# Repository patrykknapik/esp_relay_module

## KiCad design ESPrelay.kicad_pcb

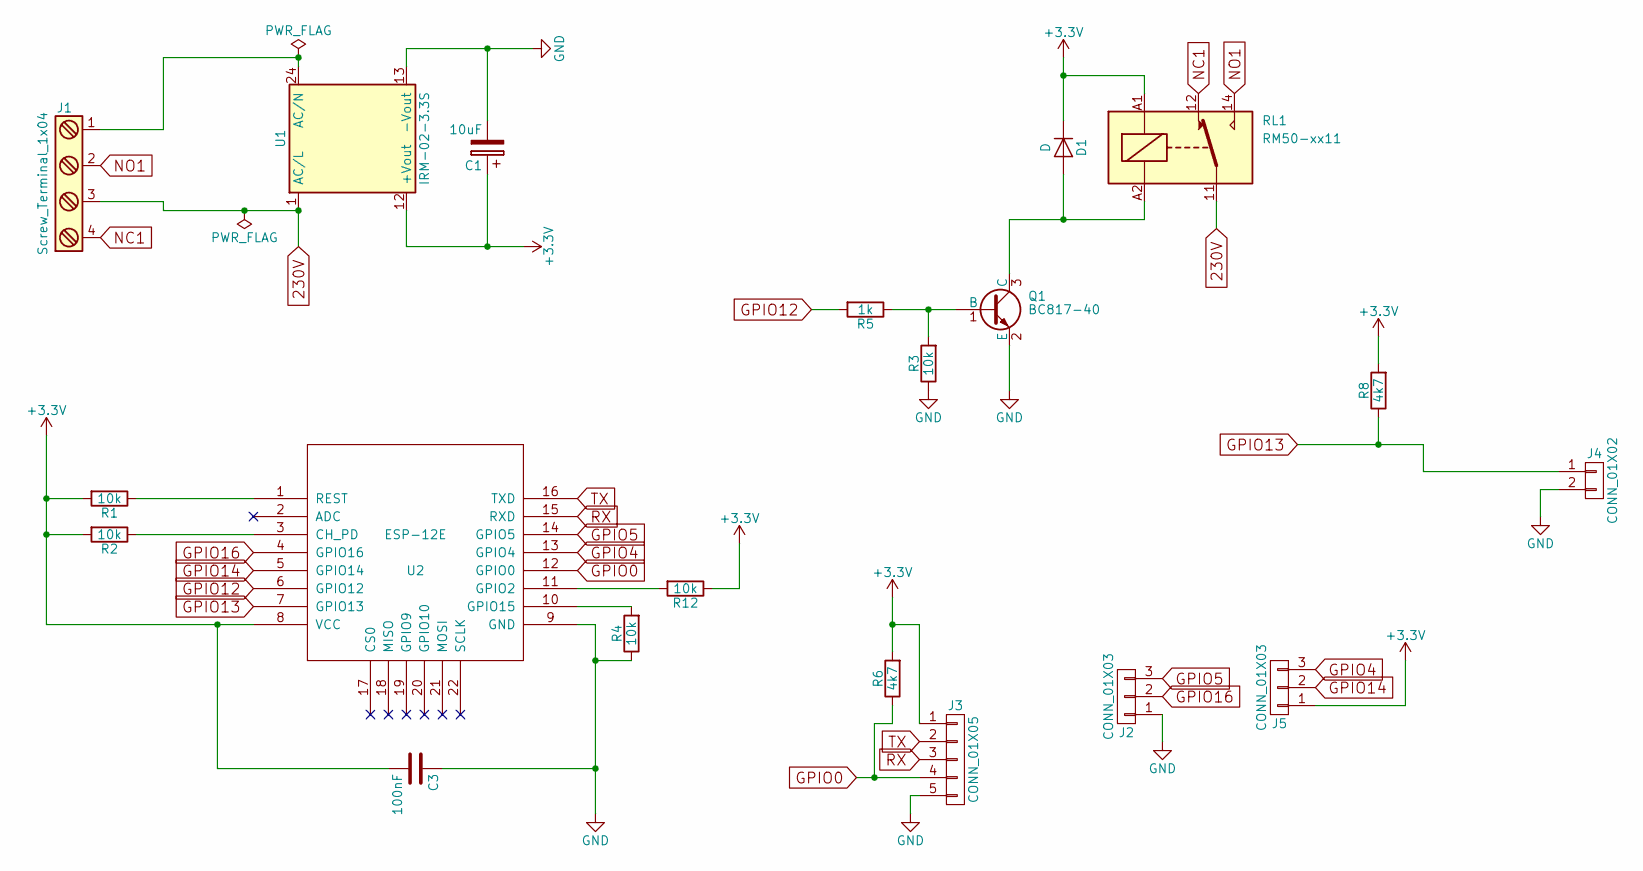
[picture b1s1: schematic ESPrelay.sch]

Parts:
C1: 10uF; CP_Tantalum_Case-B_EIA-3528-21_Hand
C3: 100nF; C_0805_HandSoldering
D1: D; D_MiniMELF_Handsoldering
J1: Screw_Terminal_1x04; bornier4
J2, J5: CONN_01X03; Pin_Header_Straight_1x03_Pitch2.54mm
J3: CONN_01X05; Pin_Header_Straight_1x05_Pitch2.54mm
J4: CONN_01X02; Pin_Header_Straight_1x02_Pitch2.54mm
Q1: BC817-40; SOT-23_Handsoldering
R1, R2, R3, R4, R12: 10k; R_0805_HandSoldering
R5: 1k; R_0805_HandSoldering
R6, R8: 4k7; R_0805_HandSoldering
RL1: RM50-xx11; Relpol_RM50-3011
U1: IRM-02-3.3S; ACDC-Converter_MeanWell-IRM-02-XS
U2: ESP-12E; ESP-12E_SMD

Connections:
230V: J1.3, RL1.11, U1.1 (AC/L)
+3V3: C1.1, C3.2, D1.1 (K), J3.1, J5.1, R1.2, R2.2, R6.2, R8.2, R12.1, RL1.A1, U1.12 (+Vout), U2.8 (VCC)
GND: C1.2, C3.1, J2.1, J3.5, J4.2, Q1.2 (E), R3.1, R4.1, U1.13 (-Vout), U2.9 (GND)
GPIO0: J3.4, R6.1, U2.12 (GPIO0)
GPIO4: J5.3, U2.13 (GPIO4)
GPIO5: J2.3, U2.14 (GPIO5)
GPIO12: R5.2, U2.6 (GPIO12)
GPIO13: J4.1, R8.1, U2.7 (GPIO13)
GPIO14: J5.2, U2.5 (GPIO14)
GPIO16: J2.2, U2.4 (GPIO16)
NC1: J1.4, RL1.12
NO1: J1.2, RL1.14
unnamed: D1.2 (A), Q1.3 (C), RL1.A2
unnamed: J1.1, U1.24 (AC/N)
unnamed: Q1.1 (B), R3.2, R5.1
unnamed: R1.1, U2.1 (REST)
unnamed: R2.1, U2.3 (CH_PD)
unnamed: R4.2, U2.10 (GPIO15)
unnamed: R12.2, U2.11 (GPIO2)
RX: J3.3, U2.15 (RXD)
TX: J3.2, U2.16 (TXD)

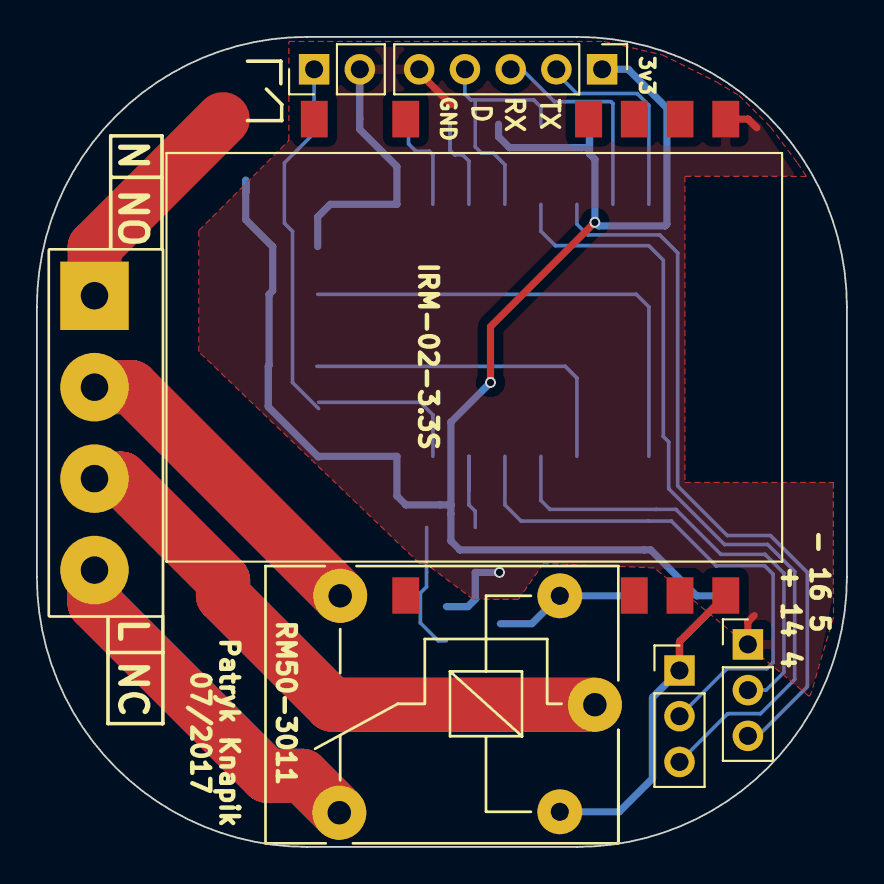
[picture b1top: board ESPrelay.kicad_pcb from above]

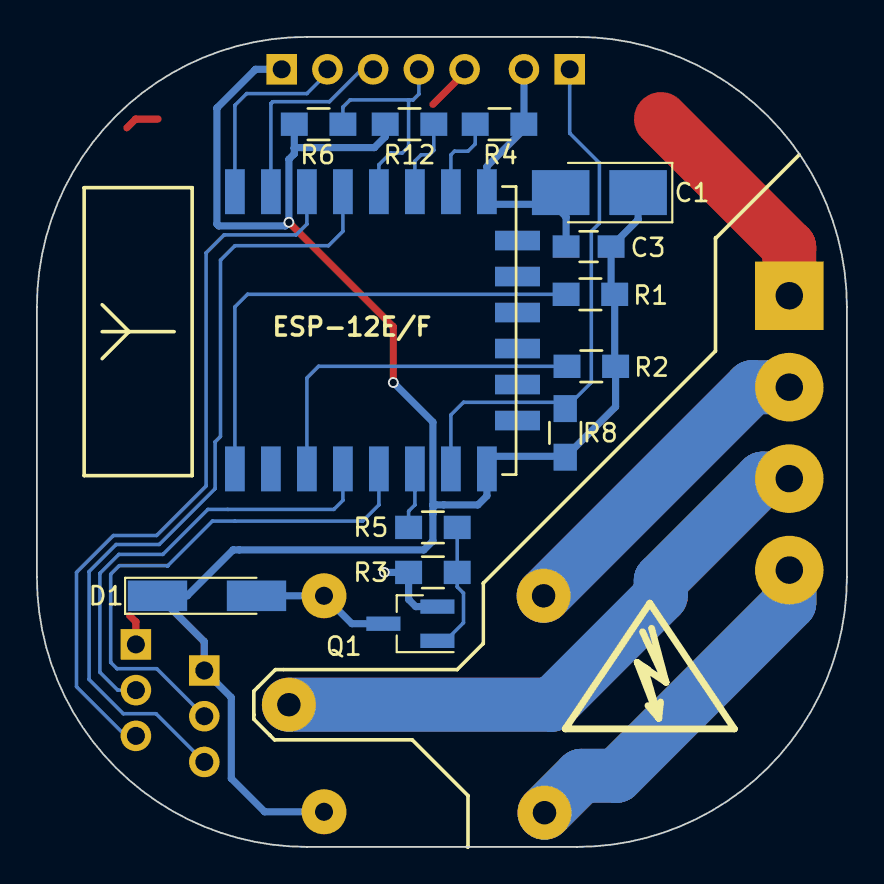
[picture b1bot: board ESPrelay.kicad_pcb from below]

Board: 2 copper layers, 45.0 x 45.0 mm, 20 parts (13 on the bottom side), 21 nets.

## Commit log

2020-05-08 commit for github
2020-07-13 Create LICENSE
